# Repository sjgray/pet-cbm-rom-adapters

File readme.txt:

PET/CBM Multi-ROM Adapters
==========================

These adapters allow you to combine multiple 4K ROMS
into one 64K ROM and select them via separate switches
or dip-switch.

The following are available:

1) PET-CBM-MULTIROM
2) MULTI-EDIT-ROM
3) 2332-MultiROM-PLCC

DECRIPTIONS
-----------

1) PET-CBM-MULTIROM

  - Up to 16 ROMs in one.
  - 4-position DIP SWITCH or off-board switches
  - DIP-SWITH section is removable
  - Suitable for adjacent ROM sockets on 4000/8000 boards
  - Suitable for 8296 KERNAL, EDIT, or BASIC sockets
  - Suitable for single 8296 OPTION rom socket
  - NOT suitable for both adjacent 8296 OPTION sockets
  - NOT suitable for SuperPET firmware ROMs

2) MULTI-EDIT-ROM

  - Up to 16 ROMs in one.
  - 4-position DIP SWITCH or off-board switches
  - Suitable for SuperPET EDIT, KERNAL and BASIC ROM sockets,
    but NOT adjacent sockets due to width of board

3) 2332-MultiROM-PLCC
  - Generally for PET ROM sockets
  - Replace any 2332 Masked ROM with a Winbond W27C010 or 0W27C020
  - Up to 16 4K banks
  - Board is same width as socket and only slightly longer

More information is available on the web:

http://www.cbmsteve.ca
http://www.cbmsteve.ca/multirom/index.html

Steve

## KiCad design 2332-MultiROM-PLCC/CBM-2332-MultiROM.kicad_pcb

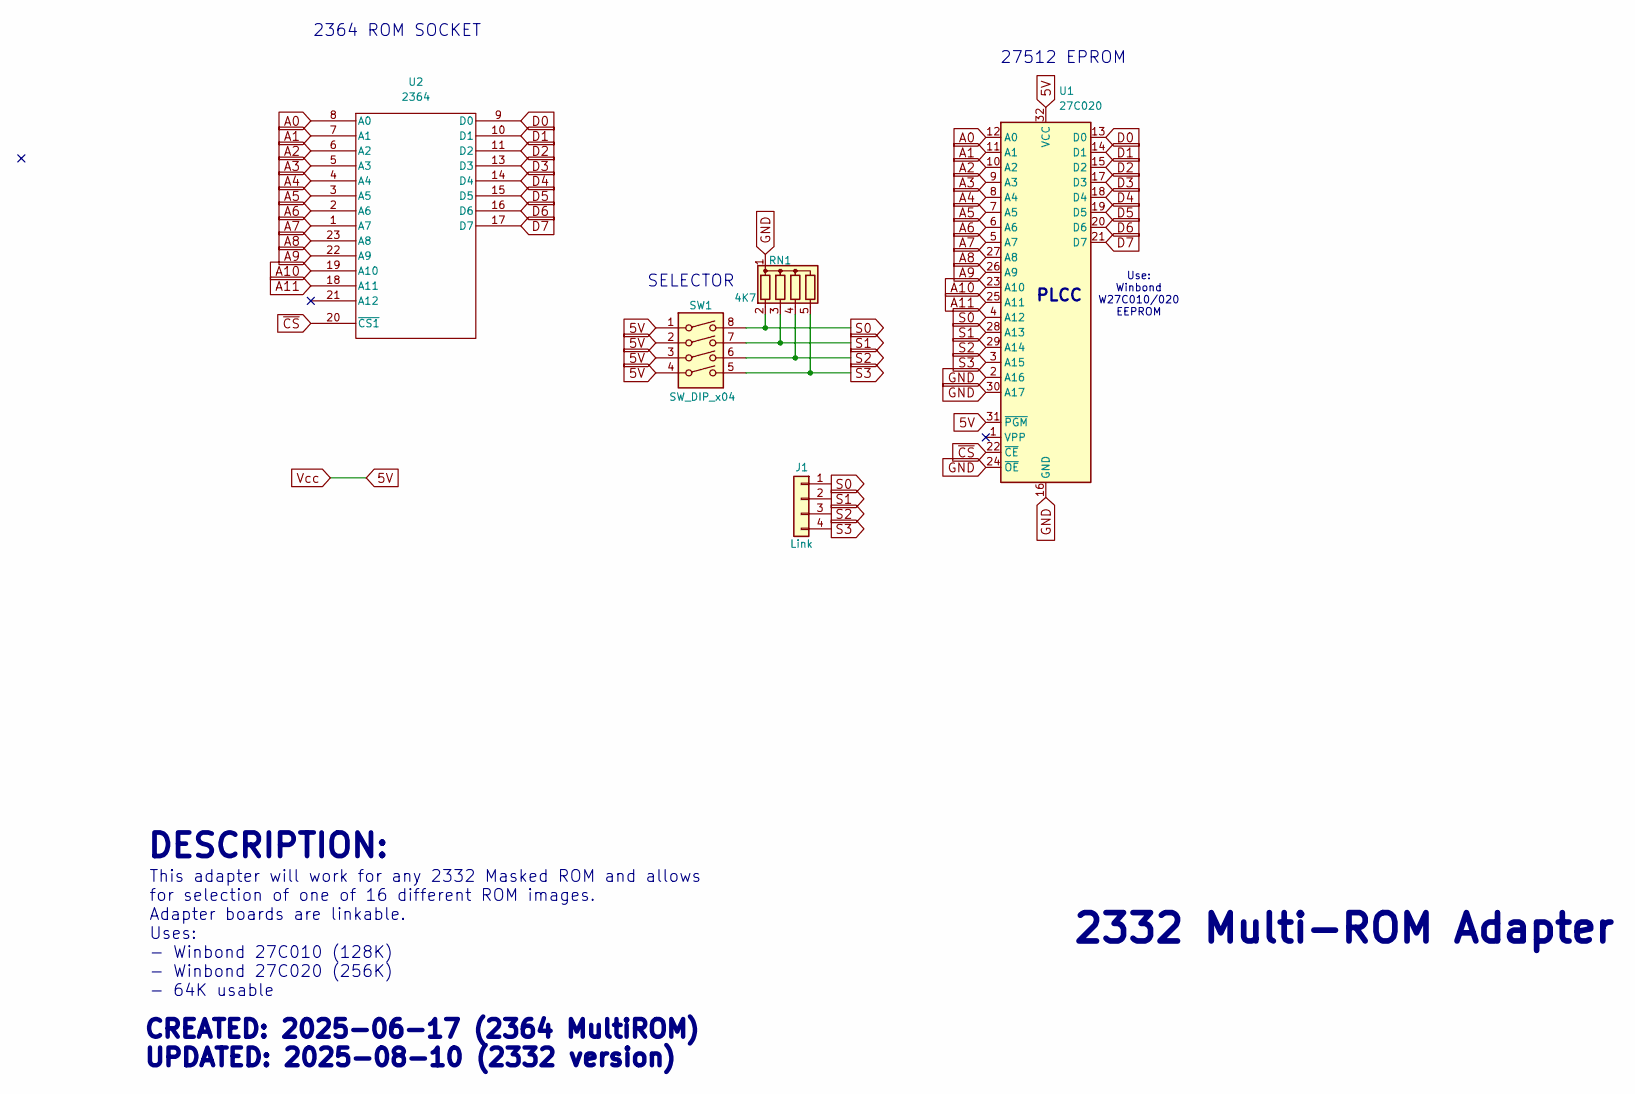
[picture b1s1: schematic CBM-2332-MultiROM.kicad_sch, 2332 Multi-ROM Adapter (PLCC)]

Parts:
J1: Link; PinHeader_1x04_P2.54mm_Vertical
RN1: 4K7; R_Array_SIP5
SW1: SW_DIP_x04; SW_DIP_SPSTx04_Slide_6.7x11.72mm_W7.62mm_P2.54mm_LowProfile
U1: 27C020; PLCC-32_THT-Socket
U2: 2364; DIP-24_W15.24mm_Socket

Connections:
5V: SW1.1, SW1.2, SW1.3, SW1.4, U1.31 (~PGM), U1.32 (VCC), U2.24 (Vcc)
A0: U1.12 (A0), U2.8 (A0)
A1: U1.11 (A1), U2.7 (A1)
A2: U1.10 (A2), U2.6 (A2)
A3: U1.9 (A3), U2.5 (A3)
A4: U1.8 (A4), U2.4 (A4)
A5: U1.7 (A5), U2.3 (A5)
A6: U1.6 (A6), U2.2 (A6)
A7: U1.5 (A7), U2.1 (A7)
A8: U1.27 (A8), U2.23 (A8)
A9: U1.26 (A9), U2.22 (A9)
A10: U1.23 (A10), U2.19 (A10)
A11: U1.25 (A11), U2.18 (A11)
D0: U1.13 (D0), U2.9 (D0)
D1: U1.14 (D1), U2.10 (D1)
D2: U1.15 (D2), U2.11 (D2)
D3: U1.17 (D3), U2.13 (D3)
D4: U1.18 (D4), U2.14 (D4)
D5: U1.19 (D5), U2.15 (D5)
D6: U1.20 (D6), U2.16 (D6)
D7: U1.21 (D7), U2.17 (D7)
GND: RN1.1 (common), U1.2 (A16), U1.16 (GND), U1.24 (~OE), U1.30 (A17), U2.12 (GND)
S0: J1.1, RN1.2 (R1), SW1.8, U1.4 (A12)
S1: J1.2, RN1.3 (R2), SW1.7, U1.28 (A13)
S2: J1.3, RN1.4 (R3), SW1.6, U1.29 (A14)
S3: J1.4, RN1.5 (R4), SW1.5, U1.3 (A15)
~CS: U1.22 (~CE), U2.20 (~CS1)

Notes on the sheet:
CREATED: 2025-06-17 (2364 MultiROM) UPDATED: 2025-08-10 (2332 version)
This adapter will work for any 2332 Masked ROM and allows for selection of one of 16 different ROM images. Adapter boards are linkable. Uses: - Winbond 27C010 (128K) - Winbond 27C020 (256K) - 64K usable
2364 ROM SOCKET
PLCC
Use: Winbond W27C010/020 EEPROM
27512 EPROM
SELECTOR
DESCRIPTION:
2332 Multi-ROM Adapter

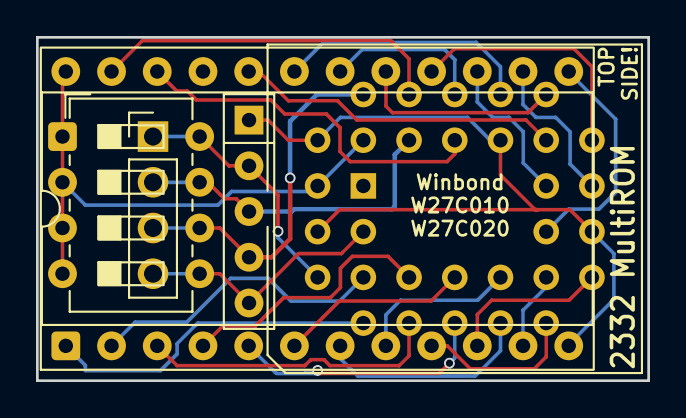
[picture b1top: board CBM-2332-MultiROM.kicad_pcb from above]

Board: 2 copper layers, 34.0 x 19.1 mm, 5 parts (0 on the bottom side), 27 nets.

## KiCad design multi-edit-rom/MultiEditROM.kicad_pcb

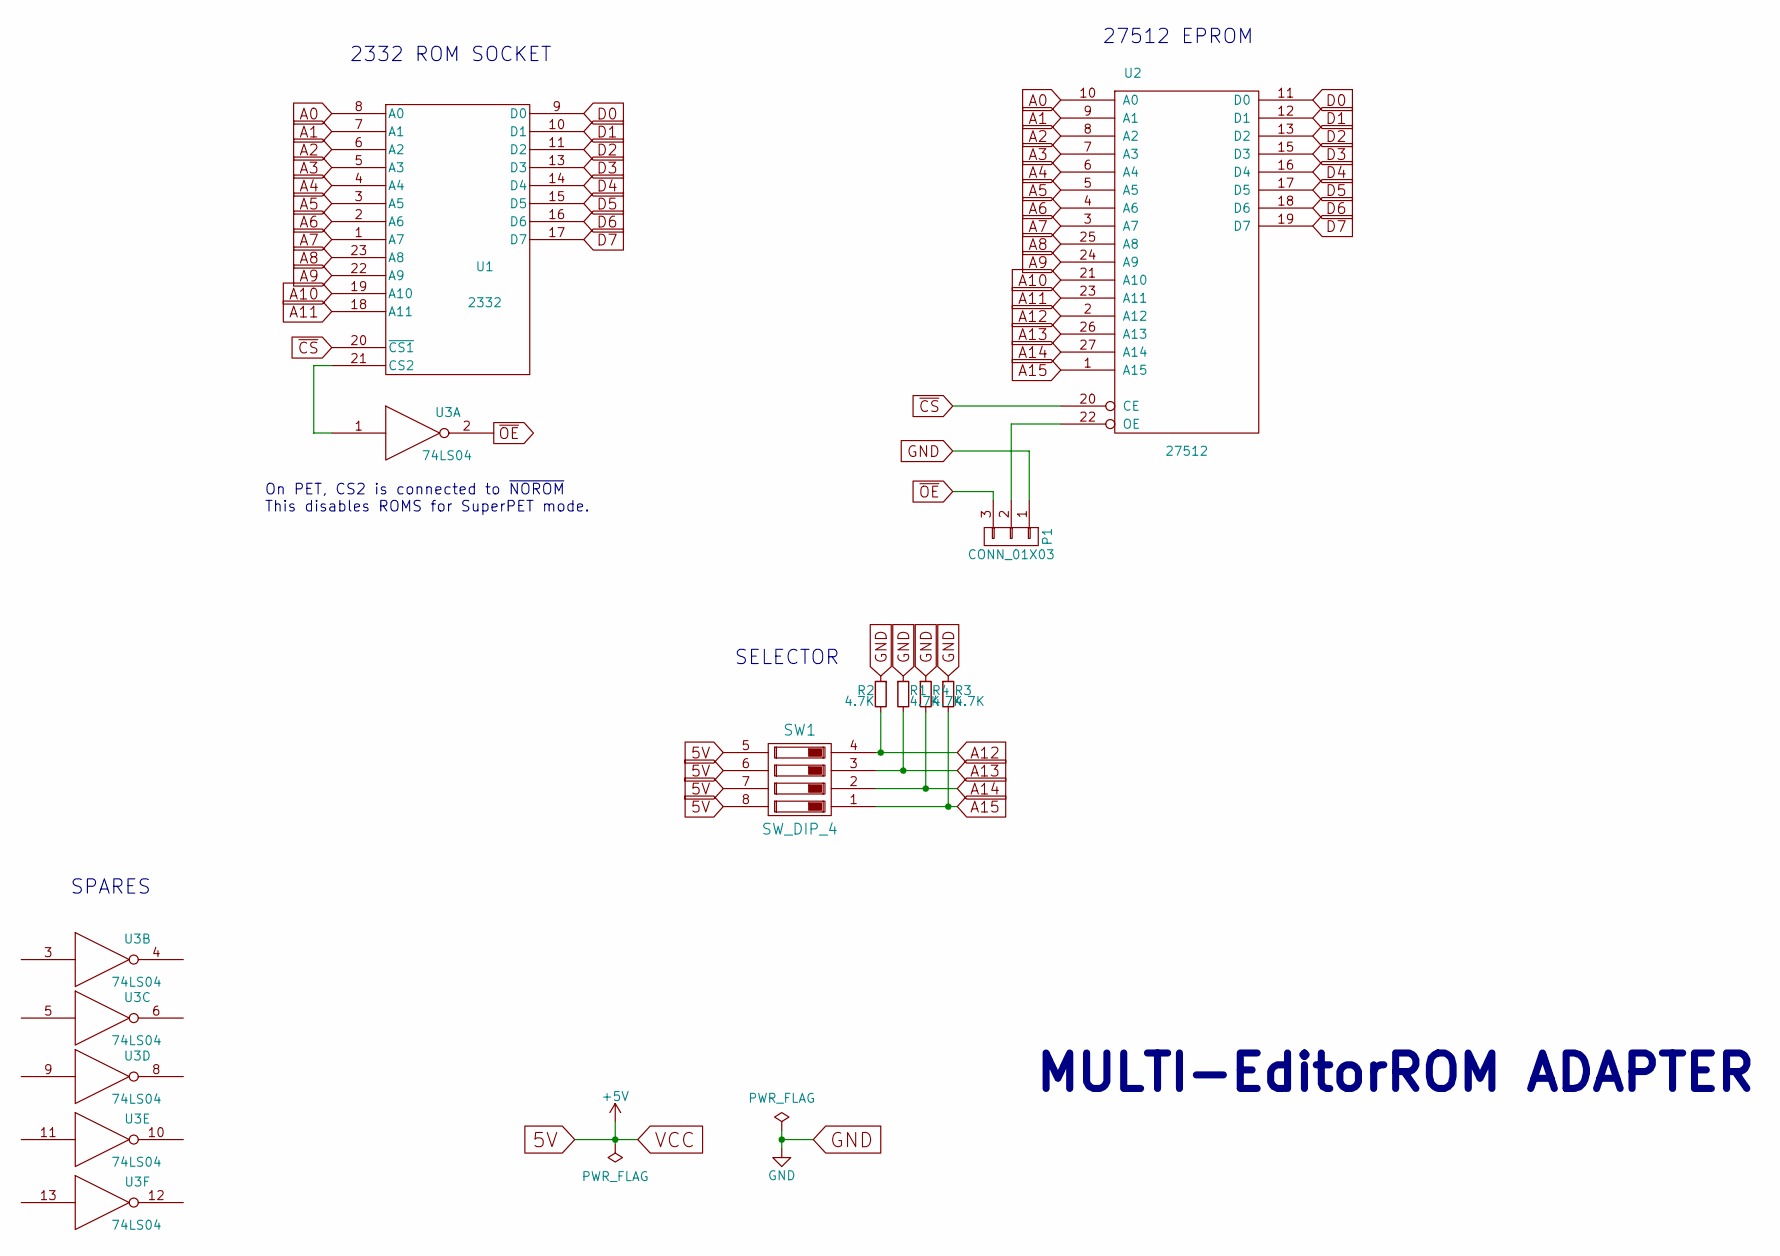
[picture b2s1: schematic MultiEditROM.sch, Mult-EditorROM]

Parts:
P1: CONN_01X03; Pin_Header_Straight_1x03_Pitch1.27mm
R1, R2, R3, R4: 4.7K; R_Axial_DIN0204_L3.6mm_D1.6mm_P5.08mm_Horizontal
SW1: SW_DIP_4; DIP-8_W7.62mm_LongPads
U1: 2332; DIP-24_W15.24mm_LongPads
U2: 27512; DIP-28_W15.24mm_LongPads
U3: 74LS04; DIP-14_W7.62mm_LongPads

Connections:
5V: SW1.5, SW1.6, SW1.7, SW1.8, U1.24 (Vcc), U2.28 (VCC), U3.14 (VCC)
A0: U1.8 (A0), U2.10 (A0)
A1: U1.7 (A1), U2.9 (A1)
A2: U1.6 (A2), U2.8 (A2)
A3: U1.5 (A3), U2.7 (A3)
A4: U1.4 (A4), U2.6 (A4)
A5: U1.3 (A5), U2.5 (A5)
A6: U1.2 (A6), U2.4 (A6)
A7: U1.1 (A7), U2.3 (A7)
A8: U1.23 (A8), U2.25 (A8)
A9: U1.22 (A9), U2.24 (A9)
A10: U1.19 (A10), U2.21 (A10)
A11: U1.18 (A11), U2.23 (A11)
A12: R2.2, SW1.4, U2.2 (A12)
A13: R1.2, SW1.3, U2.26 (A13)
A14: R4.2, SW1.2, U2.27 (A14)
A15: R3.2, SW1.1, U2.1 (A15)
D0: U1.9 (D0), U2.11 (D0)
D1: U1.10 (D1), U2.12 (D1)
D2: U1.11 (D2), U2.13 (D2)
D3: U1.13 (D3), U2.15 (D3)
D4: U1.14 (D4), U2.16 (D4)
D5: U1.15 (D5), U2.17 (D5)
D6: U1.16 (D6), U2.18 (D6)
D7: U1.17 (D7), U2.19 (D7)
GND: P1.1, R1.1, R2.1, R3.1, R4.1, U1.12 (GND), U2.14 (GND), U3.7 (GND)
unnamed: P1.2, U2.22 (OE)
unnamed: U1.21 (CS2), U3.1
~CS: U1.20 (~CS1), U2.20 (CE)
~OE: P1.3, U3.2

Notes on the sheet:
2332 ROM SOCKET
27512 EPROM
SELECTOR
MULTI-EditorROM ADAPTER
On PET, CS2 is connected to ~NOROM~ This disables ROMS for SuperPET mode.
SPARES

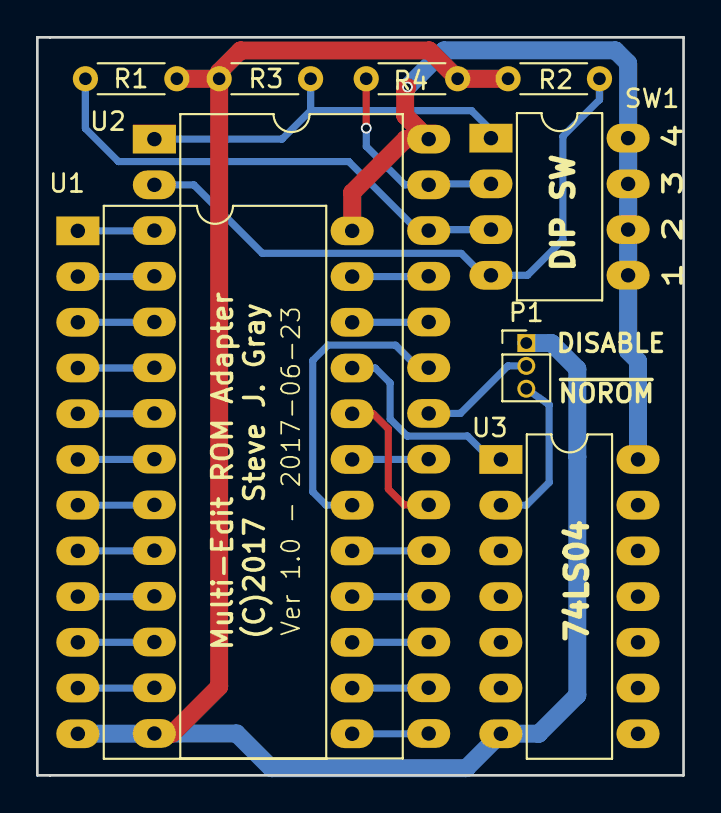
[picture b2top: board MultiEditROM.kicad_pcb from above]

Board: 2 copper layers, 35.9 x 41.0 mm, 9 parts (0 on the bottom side), 30 nets.

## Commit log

2021-08-06 :tada: Added .gitattributes & .gitignore files
2021-08-06 Initial commit
    Includes PET/CBM MultiROM and Multi-EditROM adapters
2025-01-15 Update webpage
    http://www.cbmsteve.ca/
2025-01-19 Fix link to website
    http://www.cbmsteve.ca/multirom/index.html
2025-08-13 Add 2332 MultiROM PLCC
    This has the same functionality as the other switcher but uses a Winbond PLCC EEPROM which are available, inexpensive, and smaller in size than the DIP version. The pcb is the same width as the DIP s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

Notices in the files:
2332-MultiROM-PLCC/CBM-2332-MultiROM.kicad_pcb:
(C)2025
multi-edit-rom/MultiEditROM.kicad_pcb:
(C)2017 Steve J. Gray
